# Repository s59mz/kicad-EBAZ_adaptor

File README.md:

# ebaz_adaptor
Adapter board from the EBAZ FPGA board to multiple Alinx modules and PMOD interfaces

Schematic:
[ebaz_adaptor.pdf](ebaz_adaptor.pdf)

BOM:
[ebaz_adaptor.csv](ebaz_adaptor.csv)

Gerbers:
[gerbers.zip](https://github.com/s59mz/kicad-EBAZ_adaptor/raw/main/gerbers.zip)

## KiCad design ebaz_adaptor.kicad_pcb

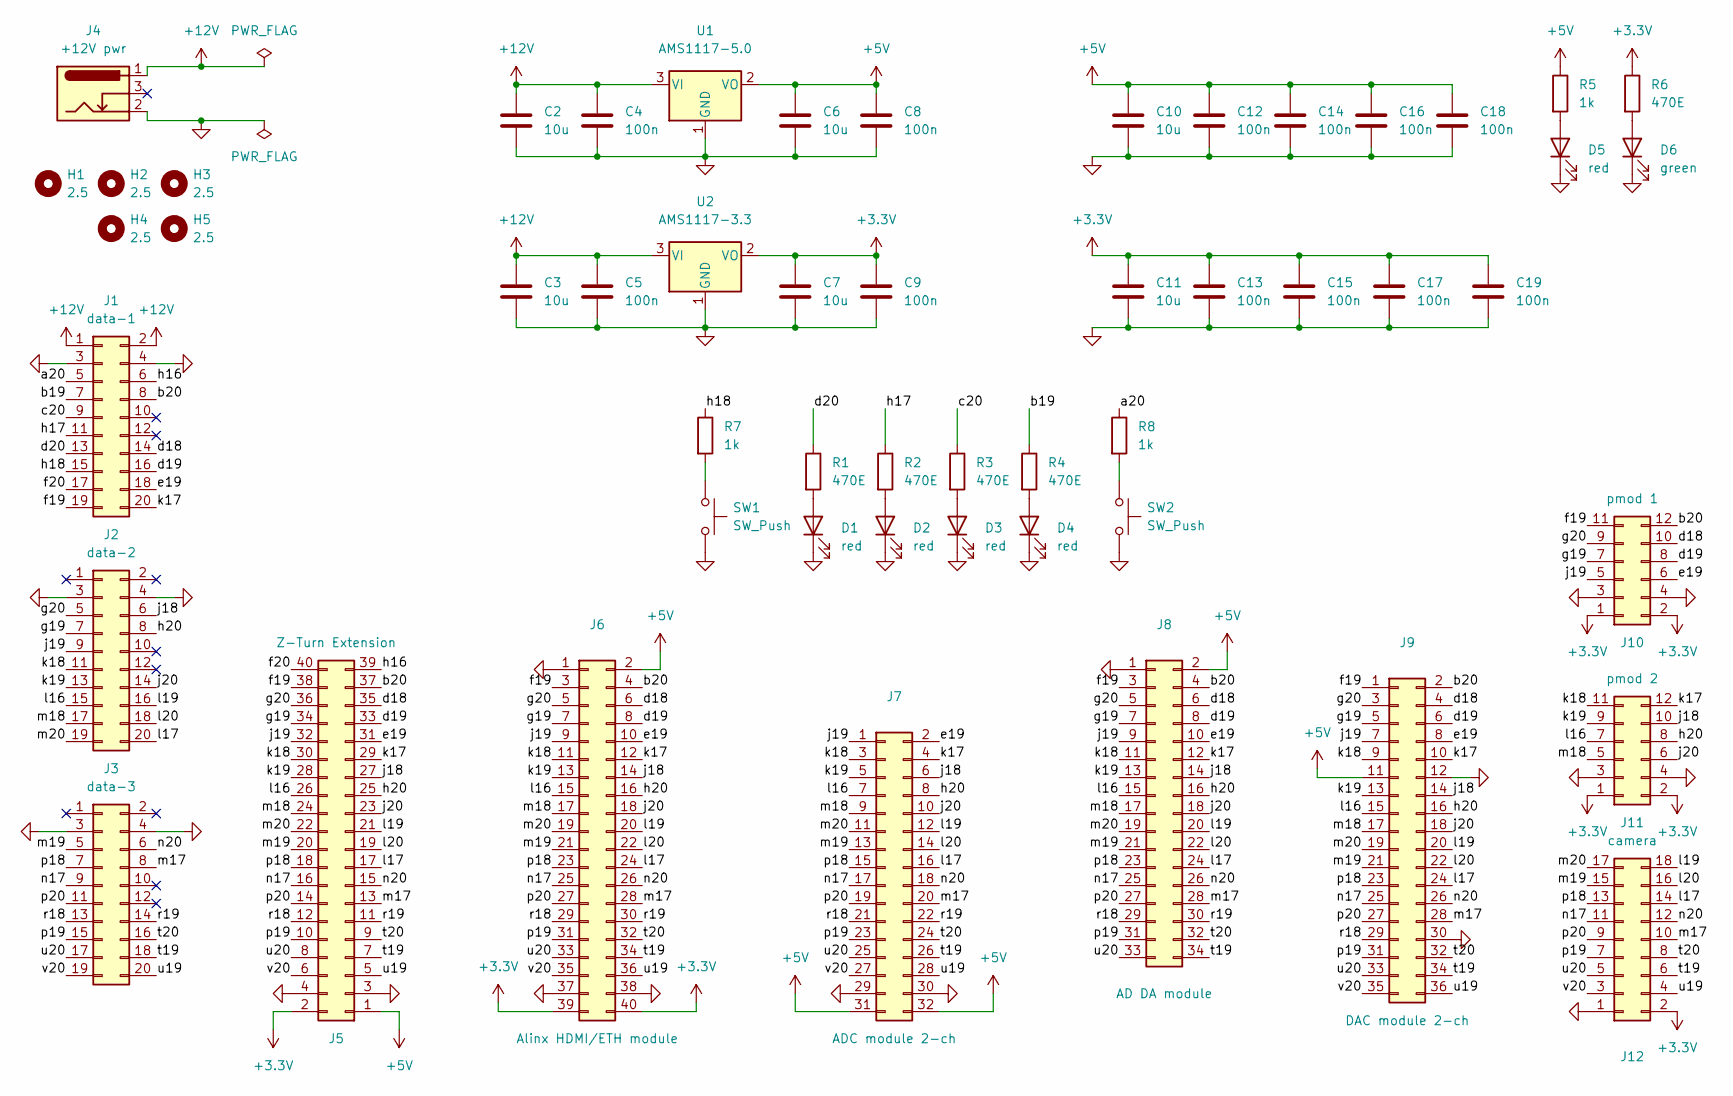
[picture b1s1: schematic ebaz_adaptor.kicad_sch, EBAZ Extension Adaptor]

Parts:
C2, C3, C6, C7, C10, C11: 10u; C_0603_1608Metric_Pad1.08x0.95mm_HandSolder
C4, C5, C8, C9, C12, C13, C14, C15, C16, C17, C18, C19: 100n; C_0603_1608Metric_Pad1.08x0.95mm_HandSolder
D1, D2, D3, D4, D5: red; LED_0603_1608Metric_Pad1.05x0.95mm_HandSolder
D6: green; LED_0603_1608Metric_Pad1.05x0.95mm_HandSolder
H1, H2, H3, H4, H5: 2.5; MountingHole_2.5mm
J1: data-1; PinSocket_2x10_P2.00mm_Horizontal
J2: data-2; PinSocket_2x10_P2.00mm_Horizontal
J3: data-3; PinSocket_2x10_P2.00mm_Horizontal
J4: +12V pwr; BarrelJack_Horizontal
J5: Z-Turn Extension; PinHeader_2x20_P2.54mm_Vertical
J6: Alinx HDMI/ETH module; PinHeader_2x20_P2.54mm_Vertical
J7: ADC module 2-ch; PinHeader_2x16_P2.54mm_Vertical
J8: AD DA module; PinHeader_2x17_P2.54mm_Vertical
J9: DAC module 2-ch; PinHeader_2x18_P2.54mm_Vertical
J10: pmod 1; PinSocket_2x06_P2.54mm_Horizontal
J11: pmod 2; PinSocket_2x06_P2.54mm_Horizontal
J12: camera; PinSocket_2x09_P2.54mm_Horizontal
R1, R2, R3, R4, R6: 470E; R_0603_1608Metric_Pad0.98x0.95mm_HandSolder
R5, R7, R8: 1k; R_0603_1608Metric_Pad0.98x0.95mm_HandSolder
SW1, SW2: SW_Push; SW_PUSH_6mm
U1: AMS1117-5.0; TO-252-2
U2: AMS1117-3.3; SOT-223-3_TabPin2

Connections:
+3.3V: C7.1, C9.1, C11.1, C13.1, C15.1, C17.1, C19.1, J5.2, J6.39, J6.40, J10.1, J10.2, J11.1, J11.2, J12.2, R6.1, U2.2 (VO)
+5V: C6.1, C8.1, C10.1, C12.1, C14.1, C16.1, C18.1, J5.1, J6.2, J7.31, J7.32, J8.2, J9.11, R5.1, U1.2 (VO)
+12V: C2.1, C3.1, C4.1, C5.1, J1.1, J1.2, J4.1, U1.3 (VI), U2.3 (VI)
/a20: J1.5, R8.1
/b19: J1.7, R4.1
/b20: J1.8, J5.37, J6.4, J8.4, J9.2, J10.12
/c20: J1.9, R3.1
/d18: J1.14, J5.35, J6.6, J8.6, J9.4, J10.10
/d19: J1.16, J5.33, J6.8, J8.8, J9.6, J10.8
/d20: J1.13, R1.1
/e19: J1.18, J5.31, J6.10, J7.2, J8.10, J9.8, J10.6
/f19: J1.19, J5.38, J6.3, J8.3, J9.1, J10.11
/f20: J1.17, J5.40
/g19: J2.7, J5.34, J6.7, J8.7, J9.5, J10.7
/g20: J2.5, J5.36, J6.5, J8.5, J9.3, J10.9
/h16: J1.6, J5.39
/h17: J1.11, R2.1
/h18: J1.15, R7.1
/h20: J2.8, J5.25, J6.16, J7.8, J8.16, J9.16, J11.8
/j18: J2.6, J5.27, J6.14, J7.6, J8.14, J9.14, J11.10
/j19: J2.9, J5.32, J6.9, J7.1, J8.9, J9.7, J10.5
/j20: J2.14, J5.23, J6.18, J7.10, J8.18, J9.18, J11.6
/k17: J1.20, J5.29, J6.12, J7.4, J8.12, J9.10, J11.12
/k18: J2.11, J5.30, J6.11, J7.3, J8.11, J9.9, J11.11
/k19: J2.13, J5.28, J6.13, J7.5, J8.13, J9.13, J11.9
/l16: J2.15, J5.26, J6.15, J7.7, J8.15, J9.15, J11.7
/l17: J2.20, J5.17, J6.24, J7.16, J8.24, J9.24, J12.14
/l19: J2.16, J5.21, J6.20, J7.12, J8.20, J9.20, J12.18
/l20: J2.18, J5.19, J6.22, J7.14, J8.22, J9.22, J12.16
/m17: J3.8, J5.13, J6.28, J7.20, J8.28, J9.28, J12.10
/m18: J2.17, J5.24, J6.17, J7.9, J8.17, J9.17, J11.5
/m19: J3.5, J5.20, J6.21, J7.13, J8.21, J9.21, J12.15
/m20: J2.19, J5.22, J6.19, J7.11, J8.19, J9.19, J12.17
/n17: J3.9, J5.16, J6.25, J7.17, J8.25, J9.25, J12.11
/n20: J3.6, J5.15, J6.26, J7.18, J8.26, J9.26, J12.12
/p18: J3.7, J5.18, J6.23, J7.15, J8.23, J9.23, J12.13
/p19: J3.15, J5.10, J6.31, J7.23, J8.31, J9.31, J12.7
/p20: J3.11, J5.14, J6.27, J7.19, J8.27, J9.27, J12.9
/r18: J3.13, J5.12, J6.29, J7.21, J8.29, J9.29
/r19: J3.14, J5.11, J6.30, J7.22, J8.30
/t19: J3.18, J5.7, J6.34, J7.26, J8.34, J9.34, J12.6
/t20: J3.16, J5.9, J6.32, J7.24, J8.32, J9.32, J12.8
/u19: J3.20, J5.5, J6.36, J7.28, J9.36, J12.4
/u20: J3.17, J5.8, J6.33, J7.25, J8.33, J9.33, J12.5
/v20: J3.19, J5.6, J6.35, J7.27, J9.35, J12.3
GND: C2.2, C3.2, C4.2, C5.2, C6.2, C7.2, C8.2, C9.2, C10.2, C11.2, C12.2, C13.2, C14.2, C15.2, C16.2, C17.2, C18.2, C19.2, D1.1 (K), D2.1 (K), D3.1 (K), D4.1 (K), D5.1 (K), D6.1 (K), J1.3, J1.4, J2.3, J2.4, J3.3, J3.4, J4.2, J5.3, J5.4, J6.1, J6.37, J6.38, J7.29, J7.30, J8.1, J9.12, J9.30, J10.3, J10.4, J11.3, J11.4, J12.1, SW1.2, SW2.2, U1.1 (GND), U2.1 (GND)
unnamed: D1.2 (A), R1.2
unnamed: D2.2 (A), R2.2
unnamed: D3.2 (A), R3.2
unnamed: D4.2 (A), R4.2
unnamed: D5.2 (A), R5.2
unnamed: D6.2 (A), R6.2
unnamed: R7.2, SW1.1
unnamed: R8.2, SW2.1

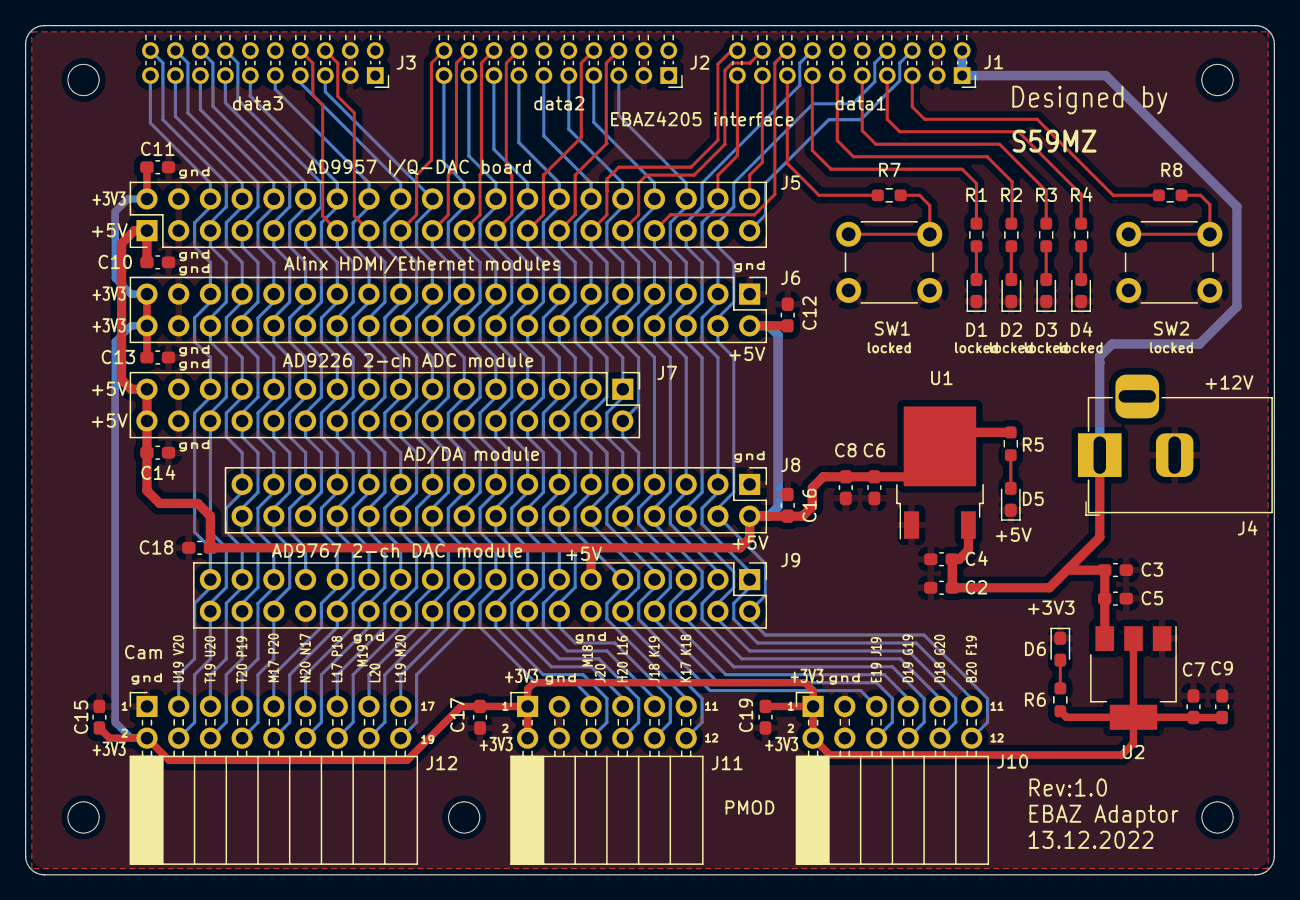
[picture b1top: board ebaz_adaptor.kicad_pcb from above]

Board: 2 copper layers, 100.0 x 68.0 mm, 53 parts (0 on the bottom side), 54 nets.

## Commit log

2024-08-11 add screenshots
